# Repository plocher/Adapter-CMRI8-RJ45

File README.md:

# Adapter-CMRI8-RJ45
## License: CERN Open Hardware Licence v1.2

CMRI boards have traditionally used Molex KK 0.156 pitch I/O pins, which required crimping matching connectors onto layout wiring.
This adapter board converts them into RJ-45 style used by common network cables.

Crimping to RH45 connectors is (IMO at least) much simpler than the alternative.

Another of these boards can be used at the other end of the 8-conductor
cable, but this time it can be populated with a 0.1" or 3.5mm pitch
screw terminal and mounted to the benchwork near where it's signals
are used.

  * 4.0 Added optional resistors inline for direct driving LED outputs with a default (cuttable) link for use as inputs...
  * 5.0 Added SPDT "Frog Power" 3.5mm connector pads

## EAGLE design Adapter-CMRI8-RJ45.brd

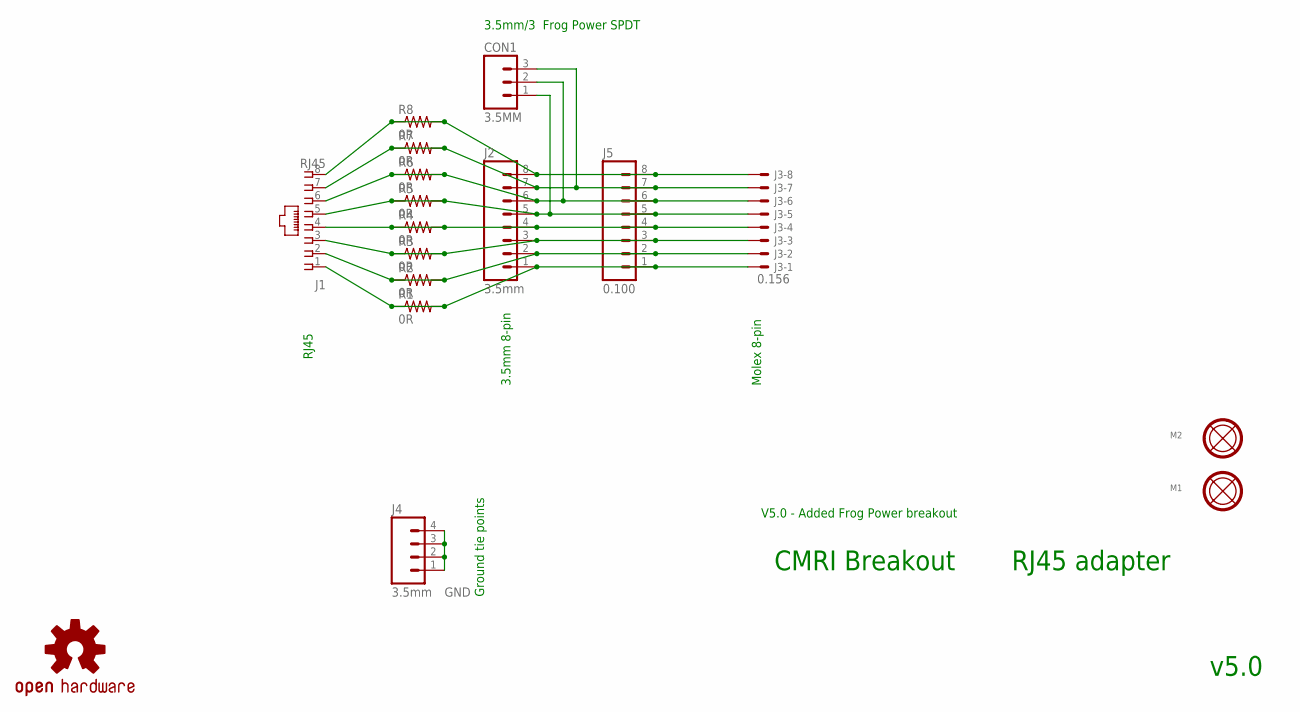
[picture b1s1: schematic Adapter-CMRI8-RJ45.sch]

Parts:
CON1: 3.5MM; SCREWTERMINAL-3.5MM-3_LOCK.007S
J1: RJ45; RJ45-NO-SHIELD
J2: 3.5mm; SCREWTERMINAL-3.5MM-8
J3: 0.156; KK-156-8-F
J4: 3.5mm; SCREWTERMINAL-3.5MM-4_LOCK
J5: 0.100; 1X08_LOCK
M1, M2: MOUNTINGHOLE
R1, R2, R3, R4, R5, R6, R7, R8: 0R; AXIAL-0.4-RES
U$1: OSHW; OSHW-LOGO-L

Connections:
GND: J4.1, J4.2, J4.3, J4.4
L1: J1.1, J2.1, J3.1, J5.1, R1.P$1 (1), R1.P$2 (2)
L2: J1.2, J2.2, J3.2, J5.2, R2.P$1 (1), R2.P$2 (2)
L3: J1.3, J2.3, J3.3, J5.3, R3.P$1 (1), R3.P$2 (2)
L4: J1.4, J2.4, J3.4, J5.4, R4.P$1 (1), R4.P$2 (2)
L5: CON1.1, J1.5, J2.5, J3.5, J5.5, R5.P$1 (1), R5.P$2 (2)
L6: CON1.2, J1.6, J2.6, J3.6, J5.6, R6.P$1 (1), R6.P$2 (2)
L7: CON1.3, J1.7, J2.7, J3.7, J5.7, R7.P$1 (1), R7.P$2 (2)
L8: J1.8, J2.8, J3.8, J5.8, R8.P$1 (1), R8.P$2 (2)

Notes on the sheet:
Molex 8-pin
3.5mm 8-pin
RJ45
CMRI Breakout
RJ45 adapter
v5.0
Ground tie points
V5.0 - Added Frog Power breakout
3.5mm/3 Frog Power SPDT

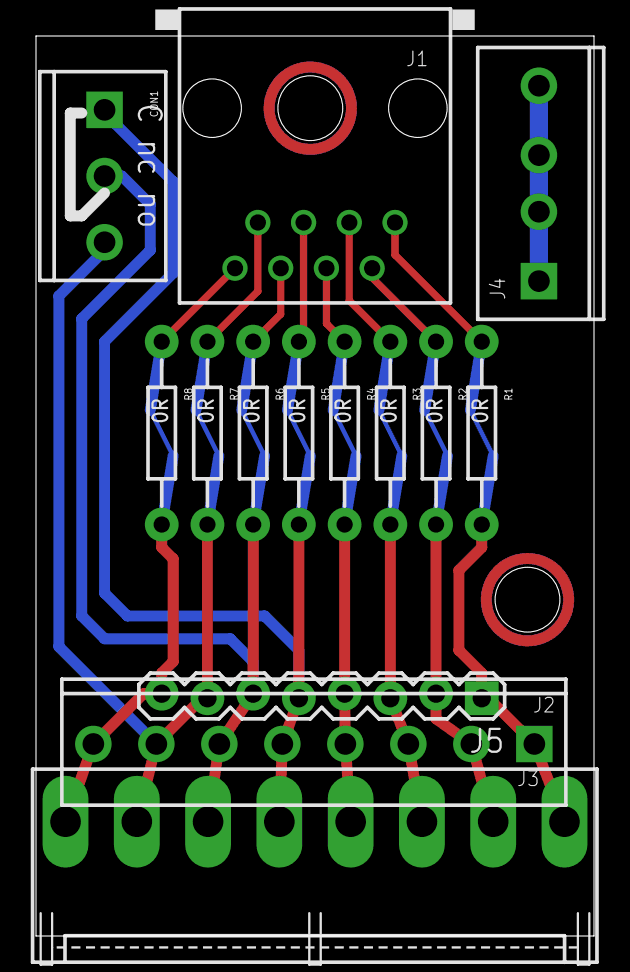
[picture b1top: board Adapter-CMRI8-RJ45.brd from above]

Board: 2 copper layers, 31.0 x 50.0 mm, 17 parts (0 on the bottom side), 9 nets.

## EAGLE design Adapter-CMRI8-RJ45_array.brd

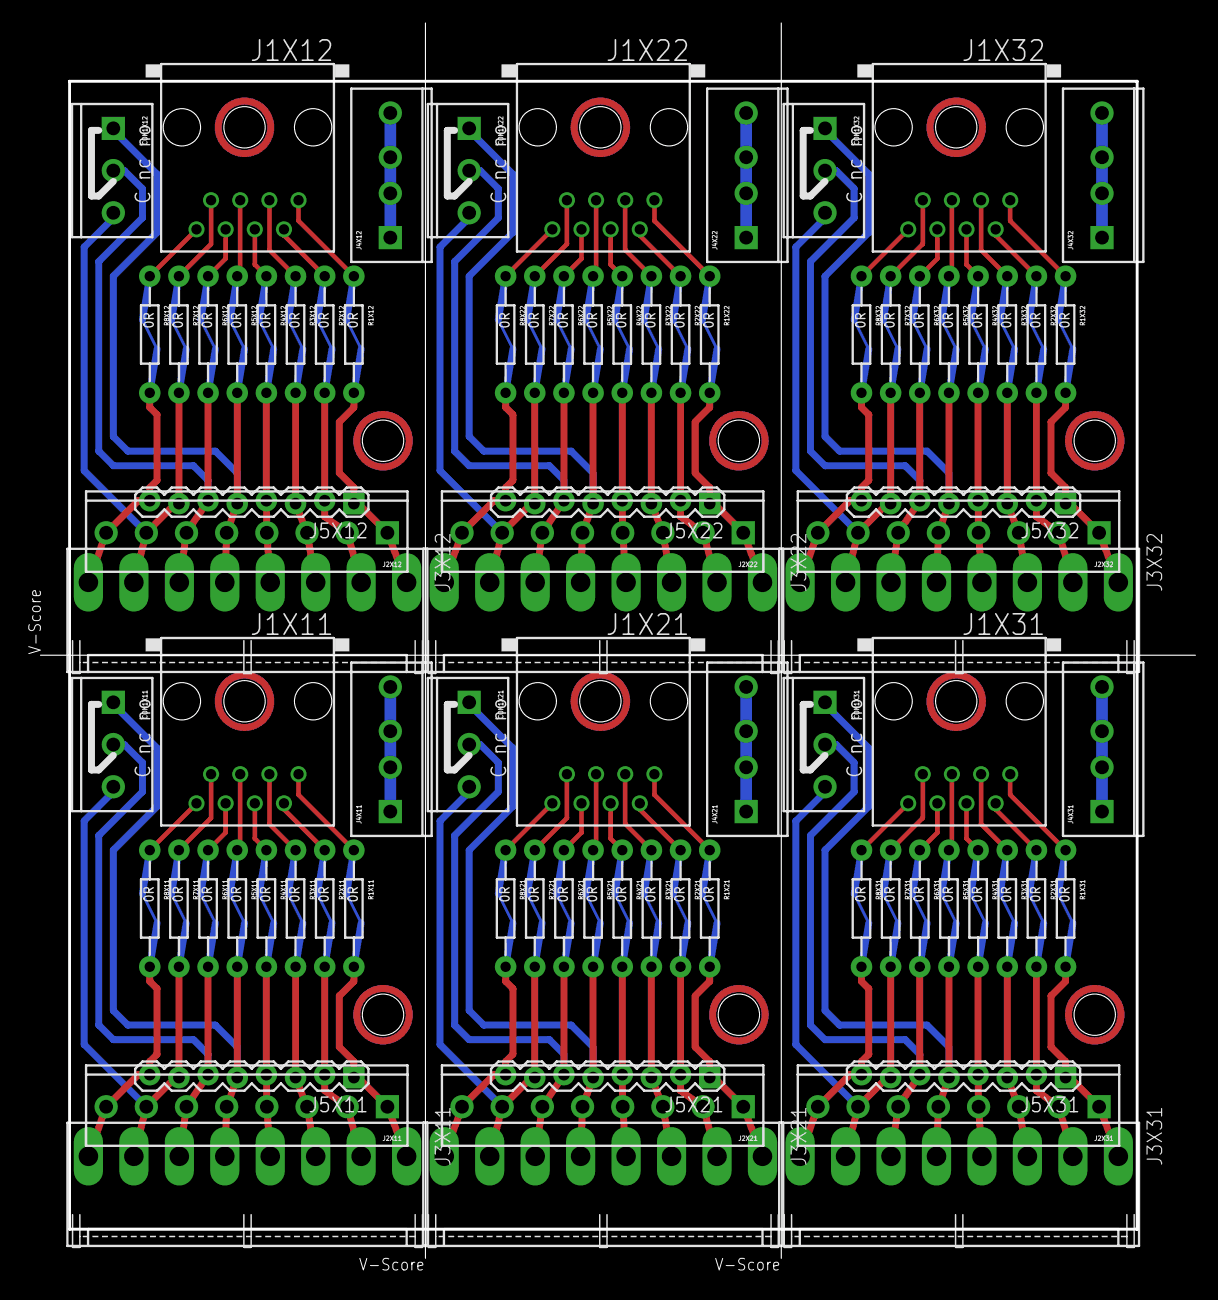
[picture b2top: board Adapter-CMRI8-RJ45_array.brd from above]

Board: 2 copper layers, 101.9 x 109.0 mm, 102 parts (0 on the bottom side), 54 nets.

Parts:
CON1X11, CON1X12, CON1X21, CON1X22, CON1X31, CON1X32: CONNECTOR-M033.5MM-LOCK; SCREWTERMINAL-3.5MM-3_LOCK.007S
J1X11, J1X12, J1X21, J1X22, J1X31, J1X32: RJ45; RJ45-NO-SHIELD
J2X11, J2X12, J2X21, J2X22, J2X31, J2X32: 3.5mm; SCREWTERMINAL-3.5MM-8
J3X11, J3X12, J3X21, J3X22, J3X31, J3X32: 0.156; KK-156-8-F
J4X11, J4X12, J4X21, J4X22, J4X31, J4X32: 3.5mm; SCREWTERMINAL-3.5MM-4_LOCK
J5X11, J5X12, J5X21, J5X22, J5X31, J5X32: 0.100; 1X08_LOCK
M1X11, M1X12, M1X21, M1X22, M1X31, M1X32, M2X11, M2X12, M2X21, M2X22, M2X31, M2X32: MOUNTINGHOLE
R1X11, R1X12, R1X21, R1X22, R1X31, R1X32, R2X11, R2X12, R2X21, R2X22, R2X31, R2X32, R3X11, R3X12, R3X21, R3X22, R3X31, R3X32, R4X11, R4X12, R4X21, R4X22, R4X31, R4X32, R5X11, R5X12, R5X21, R5X22, R5X31, R5X32, R6X11, R6X12, R6X21, R6X22, R6X31, R6X32, R7X11, R7X12, R7X21, R7X22, R7X31, R7X32, R8X11, R8X12, R8X21, R8X22, R8X31, R8X32: 0R; AXIAL-0.4-RES
U$1X11, U$1X12, U$1X21, U$1X22, U$1X31, U$1X32: DOC-OSHW-LOGO-L; OSHW-LOGO-L

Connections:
GNDX11: J4X11.1, J4X11.2, J4X11.3, J4X11.4
GNDX12: J4X12.1, J4X12.2, J4X12.3, J4X12.4
GNDX21: J4X21.1, J4X21.2, J4X21.3, J4X21.4
GNDX22: J4X22.1, J4X22.2, J4X22.3, J4X22.4
GNDX31: J4X31.1, J4X31.2, J4X31.3, J4X31.4
GNDX32: J4X32.1, J4X32.2, J4X32.3, J4X32.4
L1X11: J1X11.1, J2X11.1, J3X11.1, J5X11.1, R1X11.P$1, R1X11.P$2
L1X12: J1X12.1, J2X12.1, J3X12.1, J5X12.1, R1X12.P$1, R1X12.P$2
L1X21: J1X21.1, J2X21.1, J3X21.1, J5X21.1, R1X21.P$1, R1X21.P$2
L1X22: J1X22.1, J2X22.1, J3X22.1, J5X22.1, R1X22.P$1, R1X22.P$2
L1X31: J1X31.1, J2X31.1, J3X31.1, J5X31.1, R1X31.P$1, R1X31.P$2
L1X32: J1X32.1, J2X32.1, J3X32.1, J5X32.1, R1X32.P$1, R1X32.P$2
L2X11: J1X11.2, J2X11.2, J3X11.2, J5X11.2, R2X11.P$1, R2X11.P$2
L2X12: J1X12.2, J2X12.2, J3X12.2, J5X12.2, R2X12.P$1, R2X12.P$2
L2X21: J1X21.2, J2X21.2, J3X21.2, J5X21.2, R2X21.P$1, R2X21.P$2
L2X22: J1X22.2, J2X22.2, J3X22.2, J5X22.2, R2X22.P$1, R2X22.P$2
L2X31: J1X31.2, J2X31.2, J3X31.2, J5X31.2, R2X31.P$1, R2X31.P$2
L2X32: J1X32.2, J2X32.2, J3X32.2, J5X32.2, R2X32.P$1, R2X32.P$2
L3X11: J1X11.3, J2X11.3, J3X11.3, J5X11.3, R3X11.P$1, R3X11.P$2
L3X12: J1X12.3, J2X12.3, J3X12.3, J5X12.3, R3X12.P$1, R3X12.P$2
L3X21: J1X21.3, J2X21.3, J3X21.3, J5X21.3, R3X21.P$1, R3X21.P$2
L3X22: J1X22.3, J2X22.3, J3X22.3, J5X22.3, R3X22.P$1, R3X22.P$2
L3X31: J1X31.3, J2X31.3, J3X31.3, J5X31.3, R3X31.P$1, R3X31.P$2
L3X32: J1X32.3, J2X32.3, J3X32.3, J5X32.3, R3X32.P$1, R3X32.P$2
L4X11: J1X11.4, J2X11.4, J3X11.4, J5X11.4, R4X11.P$1, R4X11.P$2
L4X12: J1X12.4, J2X12.4, J3X12.4, J5X12.4, R4X12.P$1, R4X12.P$2
L4X21: J1X21.4, J2X21.4, J3X21.4, J5X21.4, R4X21.P$1, R4X21.P$2
L4X22: J1X22.4, J2X22.4, J3X22.4, J5X22.4, R4X22.P$1, R4X22.P$2
L4X31: J1X31.4, J2X31.4, J3X31.4, J5X31.4, R4X31.P$1, R4X31.P$2
L4X32: J1X32.4, J2X32.4, J3X32.4, J5X32.4, R4X32.P$1, R4X32.P$2
L5X11: CON1X11.1, J1X11.5, J2X11.5, J3X11.5, J5X11.5, R5X11.P$1, R5X11.P$2
L5X12: CON1X12.1, J1X12.5, J2X12.5, J3X12.5, J5X12.5, R5X12.P$1, R5X12.P$2
L5X21: CON1X21.1, J1X21.5, J2X21.5, J3X21.5, J5X21.5, R5X21.P$1, R5X21.P$2
L5X22: CON1X22.1, J1X22.5, J2X22.5, J3X22.5, J5X22.5, R5X22.P$1, R5X22.P$2
L5X31: CON1X31.1, J1X31.5, J2X31.5, J3X31.5, J5X31.5, R5X31.P$1, R5X31.P$2
L5X32: CON1X32.1, J1X32.5, J2X32.5, J3X32.5, J5X32.5, R5X32.P$1, R5X32.P$2
L6X11: CON1X11.2, J1X11.6, J2X11.6, J3X11.6, J5X11.6, R6X11.P$1, R6X11.P$2
L6X12: CON1X12.2, J1X12.6, J2X12.6, J3X12.6, J5X12.6, R6X12.P$1, R6X12.P$2
L6X21: CON1X21.2, J1X21.6, J2X21.6, J3X21.6, J5X21.6, R6X21.P$1, R6X21.P$2
L6X22: CON1X22.2, J1X22.6, J2X22.6, J3X22.6, J5X22.6, R6X22.P$1, R6X22.P$2
L6X31: CON1X31.2, J1X31.6, J2X31.6, J3X31.6, J5X31.6, R6X31.P$1, R6X31.P$2
L6X32: CON1X32.2, J1X32.6, J2X32.6, J3X32.6, J5X32.6, R6X32.P$1, R6X32.P$2
L7X11: CON1X11.3, J1X11.7, J2X11.7, J3X11.7, J5X11.7, R7X11.P$1, R7X11.P$2
L7X12: CON1X12.3, J1X12.7, J2X12.7, J3X12.7, J5X12.7, R7X12.P$1, R7X12.P$2
L7X21: CON1X21.3, J1X21.7, J2X21.7, J3X21.7, J5X21.7, R7X21.P$1, R7X21.P$2
L7X22: CON1X22.3, J1X22.7, J2X22.7, J3X22.7, J5X22.7, R7X22.P$1, R7X22.P$2
L7X31: CON1X31.3, J1X31.7, J2X31.7, J3X31.7, J5X31.7, R7X31.P$1, R7X31.P$2
L7X32: CON1X32.3, J1X32.7, J2X32.7, J3X32.7, J5X32.7, R7X32.P$1, R7X32.P$2
L8X11: J1X11.8, J2X11.8, J3X11.8, J5X11.8, R8X11.P$1, R8X11.P$2
L8X12: J1X12.8, J2X12.8, J3X12.8, J5X12.8, R8X12.P$1, R8X12.P$2
L8X21: J1X21.8, J2X21.8, J3X21.8, J5X21.8, R8X21.P$1, R8X21.P$2
L8X22: J1X22.8, J2X22.8, J3X22.8, J5X22.8, R8X22.P$1, R8X22.P$2
L8X31: J1X31.8, J2X31.8, J3X31.8, J5X31.8, R8X31.P$1, R8X31.P$2
L8X32: J1X32.8, J2X32.8, J3X32.8, J5X32.8, R8X32.P$1, R8X32.P$2

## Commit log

2019-12-09 added graphic
2020-05-04 updated tags
2020-06-16 Addrd SPDT frog power connector
2020-06-16 V5.0 added SPDT frog power
2020-06-18 updated docs
2020-10-05 added values for connectors
2020-10-06 normalized values

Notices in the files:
parts and their libraries:
SPCoast: http://freedomdefined.org/OSHW Creative Commons - Attribution - ShareAlike 3.0
